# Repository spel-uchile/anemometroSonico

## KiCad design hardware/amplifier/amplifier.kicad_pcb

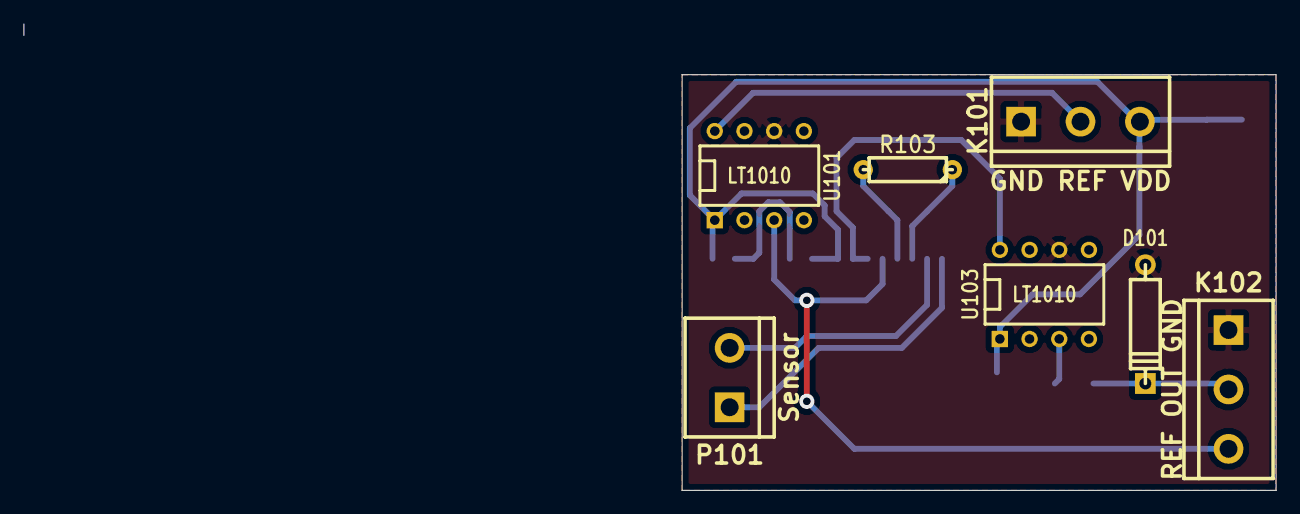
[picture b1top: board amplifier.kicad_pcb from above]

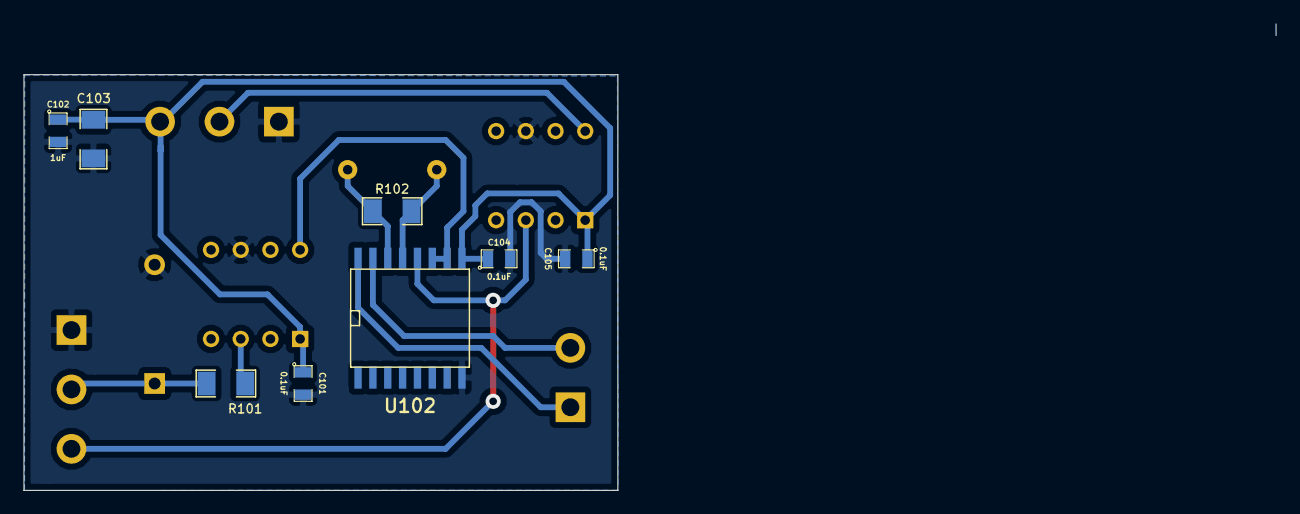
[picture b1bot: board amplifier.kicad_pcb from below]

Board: 2 copper layers, 107.1 x 39.9 mm, 15 parts (8 on the bottom side), 11 nets.

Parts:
C101, C104, C105: 0.1uF; SM0805
C102: 1uF; SM0805
C103: 10uF; SM1206
D101: 1N4732; D4
K101: GND REF VDD; bornier3
K102: REF OUT GND; bornier3
P101: Sensor; bornier2
R101: 1K; SM1206
R102: R; SM1206
R103: R; R3-LARGE_PADS
U101, U103: LT1010; DIP-8__300
U102: INA2128; SO16L

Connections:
/Se1: P101.2, U102.15
/Se2: P101.1, U102.16
/Vout: D101.2, K102.2, R101.1
/Vref: K102.3, U101.3, U102.12
/VrefIN: K101.2, U101.8
GND: C101.2, C102.2, C103.2, C104.2, C105.2, D101.1, K101.1, K102.1, U101.6, U102.8, U103.6
unnamed: U102.10, U102.11, U103.8
unnamed: R101.2, U103.3
unnamed: R102.2, R103.2, U102.13
unnamed: R102.1, R103.1, U102.14
VDD: C101.1, C102.1, C103.1, C104.1, C105.1, K101.3, U101.1, U102.9, U103.1

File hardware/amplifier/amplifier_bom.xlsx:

Quantity | SKU Digikey | Part number | Description | Reference
3 | 1276-1003-1-ND | CL21B104KBCNNNC | Capacitor 0.1uF (0805) | C101,C104,C105
1 | 1276-1029-1-ND | CL21B105KBFNNNE | Capacitor 1uF (0805) | C102
1 | 1276-2876-1-ND | CL31A106KBHNNNE | Capacitor 10uF (1206) | C103
1 | P1.00KFCT-ND | ERJ-8ENF1001V | Resistor 1k (1206) | R101
2 | LT1010CN8#PBF-ND | LT1010CN8#PBF | Power buffer LT1010 | U101,U103
1 | ED2609-ND | OSTTC022162 | Terminal block 2 pins | P101
2 | ED2610-ND | OSTTC032162 | Terminal block 3 pins | K101,K102
1 | INA2128UA-ND | INA2128UA | Instrumentation amplifier INA2128 | U102
1 | 1N4732ADICT-ND | 1N4732A-T | Zener diode 4.7v | D101
1 | P100FCT-ND | ERJ-8ENF1000V | Resistor 100 (1206) | R102

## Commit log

2013-10-22 Initial commit.
2013-10-22 Added design of ADC-USB board.
    This boards allows to connect an Analog Digital Converter to a computer
    using the USB bus.
2013-10-24 Bug fix: Increased via size for ADC-USB board.
2013-11-04 Added schematic and pcb for driving the transductors and selecting an input for the ADC.
2013-11-04 Increased via size for driver board.
2013-11-04 Replacement of analog switches with H-bridges.
2013-11-05 Excitation circuit moved to hierarchical sheet.
2013-11-05 Implementation of a C++ interface to capture data from the hardware of the anemometer.
2013-11-06 Added voltage reference VCC half using a power opamp.
2013-11-06 Added "Input Common-Mode Current Path".
2013-11-06 Replace 5V analog multiplexer by high voltage analog multiplexer.
2013-11-06 Addition of some decoupling capacitors.
2013-11-06 Added input power connector. Including input power filter and indicating leds.
2013-11-06 Change connector from 2 to 3 pins to provide connection to cable shielding.
2013-11-06 Added serial communication interface (FTDI connector).
2013-11-06 Changed led resistor value.
2013-11-06 Schematics references naming.
2013-11-06 Footprint association.
2013-11-07 Board design for the driver module.
2013-11-07 Review changes and linting.
2013-11-07 Comment typo.
2013-11-08 ADCReader binding for python using SWIG + numpy.
2013-11-08 Implementation of save and load of data using NetCDF format.
2013-11-12 Data preprocessing: Split frame and data sanity check functions
2013-11-12 Cleaner version of data_preprocessing_test.py
2013-11-12 Added plots with clean data
2013-11-18 Added amplifier board.
    Amplifier board takes an input voltage in the range of the transducer
    voltage and outputs the differential signal amplified by a constant gain
    and trimmed to 0-5V.
2013-11-19 Review changes.
2013-11-19 Added test data for identifing incomplete data.
2013-11-19 CMake function to copy python files to build directory.
2013-11-19 Revised data_preprocessing + test with unittest.py
2013-11-19 Added test files
2013-11-21 Changes for code review revision r4c2d
2013-11-21 test_data_preprocessing refactoring
2013-11-21 Fixed typos
2013-11-27 Amplifier board: change instrumentation amplifier for INA2128.
2013-11-27 Moved power connector.
2013-11-28 Placing of component designators on silk screen.
2013-11-28 Changed use of pylab to matplotlib.pyplot
2013-11-29 Initial version of the controller's firmware. Sending a number of pulses on falling edge of chip_select.
2013-11-29 Pins reasignation.
2013-11-29 Implementation of a state machine to switch between driving and listening a transducer.
    The FSM is implemented using the TIMER0 on the Match Comparator A interrupt. So
    far the two states working are DRIVE_NORTH and LISTEN_SOUTH. The start of the
    measuring sequence is delay to allow proper working of the ADC.
2013-11-29 Implementation of differential pulse.
2013-11-29 Adapt firmware to driver board.
2013-11-29 First version of bidirectional sensing.
2013-11-29 Time adjustements of driver firmware.
2013-11-29 Move rutines related to pulse generation to a separated file.
2013-11-29 Improvement to have more stable periods for pulse generation.
2013-11-29 Updates for new excitation board.
2013-11-29 Added measurement in the east west direction.
2013-11-29 Added transition states.
2013-12-16 Data logging utility.
2013-12-16 Function to read several frames.
2013-12-17 Change saving format from NetCDF to numpy.
2013-12-20 Fix small whitespace.
2013-12-23 Added bill of materials with digikey codes.
